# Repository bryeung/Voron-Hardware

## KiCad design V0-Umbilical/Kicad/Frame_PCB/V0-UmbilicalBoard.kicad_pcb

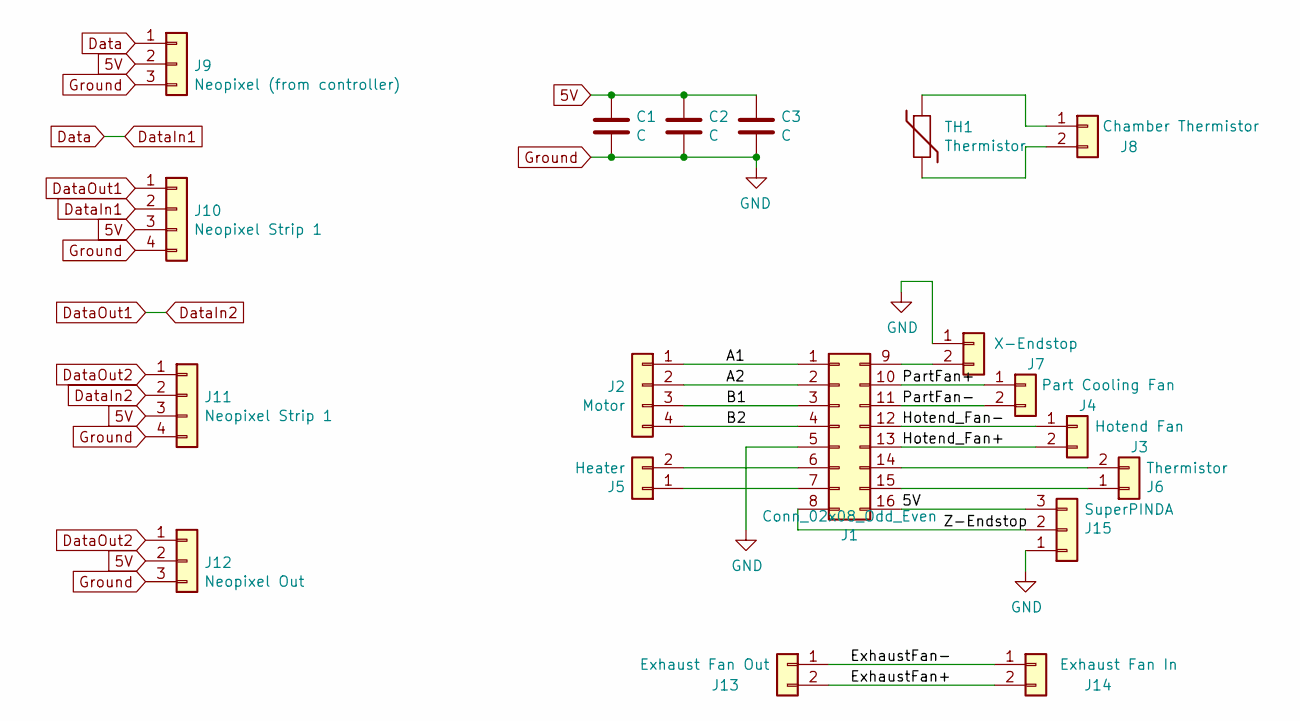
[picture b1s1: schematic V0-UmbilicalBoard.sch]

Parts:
C1, C2, C3: C; C_0805_2012Metric_Pad1.18x1.45mm_HandSolder
J1: Conn_02x08_Odd_Even; Molex_Micro-Fit_3.0_43045-1612_2x08_P3.00mm_Vertical
J2: Motor; JST_XH_B4B-XH-A_1x04_P2.50mm_Vertical
J3: Hotend Fan; JST_XH_B2B-XH-A_1x02_P2.50mm_Vertical
J4: Part Cooling Fan; JST_XH_B2B-XH-A_1x02_P2.50mm_Vertical
J5: Heater; TerminalBlock_Phoenix_MKDS-1,5-2-5.08_1x02_P5.08mm_Horizont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
J6: Thermistor; JST_XH_B2B-XH-A_1x02_P2.50mm_Vertical
J7: X-Endstop; JST_XH_B2B-XH-A_1x02_P2.50mm_Vertical
J8: Chamber Thermistor; JST_XH_B2B-XH-A_1x02_P2.50mm_Vertical
J9: Neopixel (from controller); JST_XH_B3B-XH-A_1x03_P2.50mm_Vertical
J10, J11: Neopixel Strip 1; JST_XH_B4B-XH-A_1x04_P2.50mm_Vertical
J12: Neopixel Out; JST_XH_B3B-XH-A_1x03_P2.50mm_Vertical
J13: Exhaust Fan Out; JST_XH_B2B-XH-A_1x02_P2.50mm_Vertical
J14: Exhaust Fan In; JST_XH_B2B-XH-A_1x02_P2.50mm_Vertical
J15: SuperPINDA; JST_XH_B3B-XH-A_1x03_P2.50mm_Vertical
TH1: Thermistor; R_0805_2012Metric_Pad1.20x1.40mm_HandSolder

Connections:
5V: C1.1, C2.1, C3.1, J1.16, J9.2, J10.3, J11.3, J12.2, J15.3
/A1: J1.1, J2.1
/A2: J1.2, J2.2
/B1: J1.3, J2.3
/B2: J1.4, J2.4
/ExhaustFan+: J13.2, J14.2
/ExhaustFan-: J13.1, J14.1
/Hotend_Fan+: J1.13, J3.2
/Hotend_Fan-: J1.12, J3.1
/PartFan+: J1.10, J4.1
/PartFan-: J1.11, J4.2
/Z-Endstop: J1.8, J15.2
Data: J9.1, J10.2
DataIn2: J10.1, J11.2
DataOut2: J11.1, J12.1
Ground: C1.2, C2.2, C3.2, J1.5, J7.1, J9.3, J10.4, J11.4, J12.3, J15.1
unnamed: J1.6, J5.2
unnamed: J1.7, J5.1
unnamed: J1.9, J7.2
unnamed: J1.14, J6.2
unnamed: J1.15, J6.1
unnamed: J8.1, TH1.1
unnamed: J8.2, TH1.2

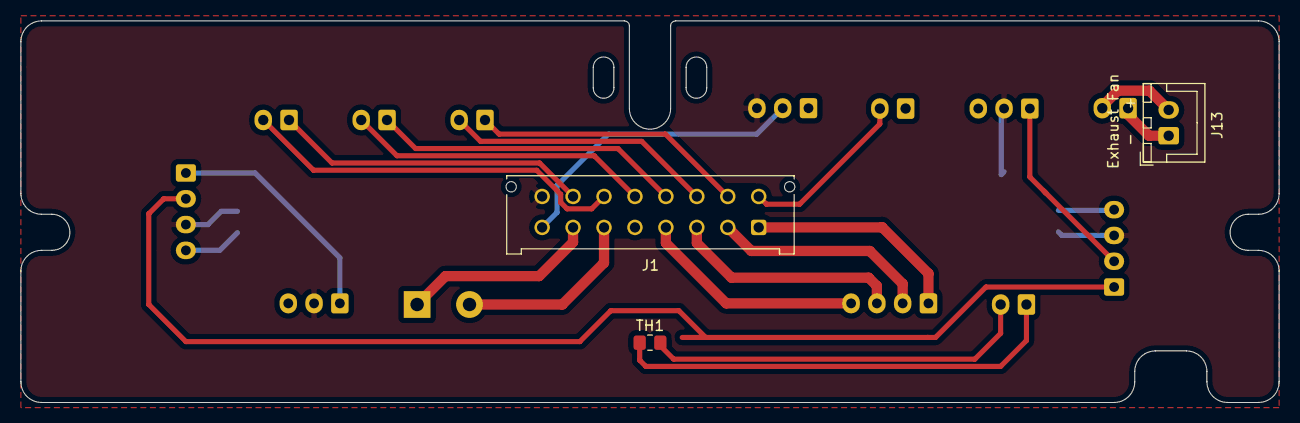
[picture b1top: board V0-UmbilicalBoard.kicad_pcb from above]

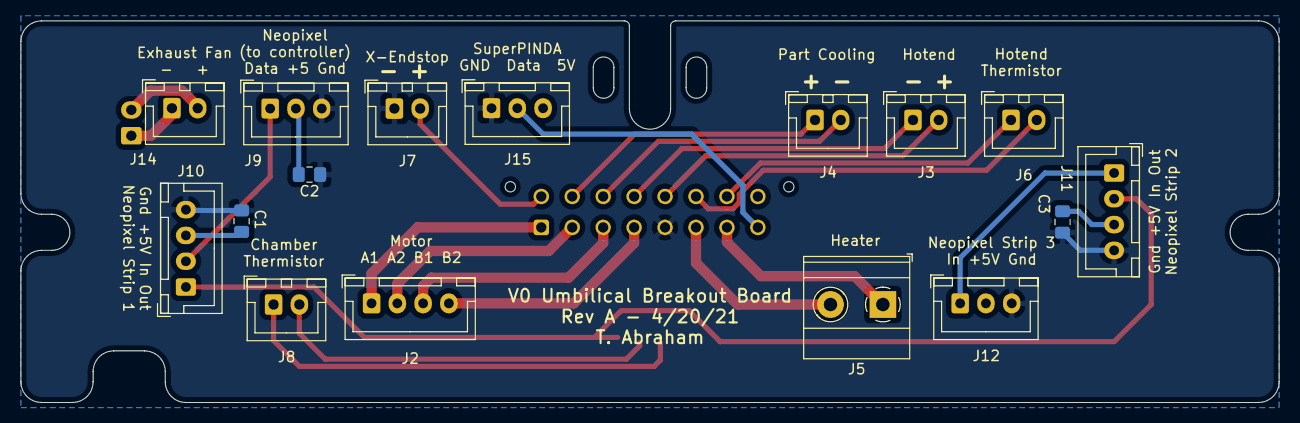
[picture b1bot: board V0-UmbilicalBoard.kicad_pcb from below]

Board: 2 copper layers, 122.0 x 37.0 mm, 19 parts (16 on the bottom side), 23 nets.

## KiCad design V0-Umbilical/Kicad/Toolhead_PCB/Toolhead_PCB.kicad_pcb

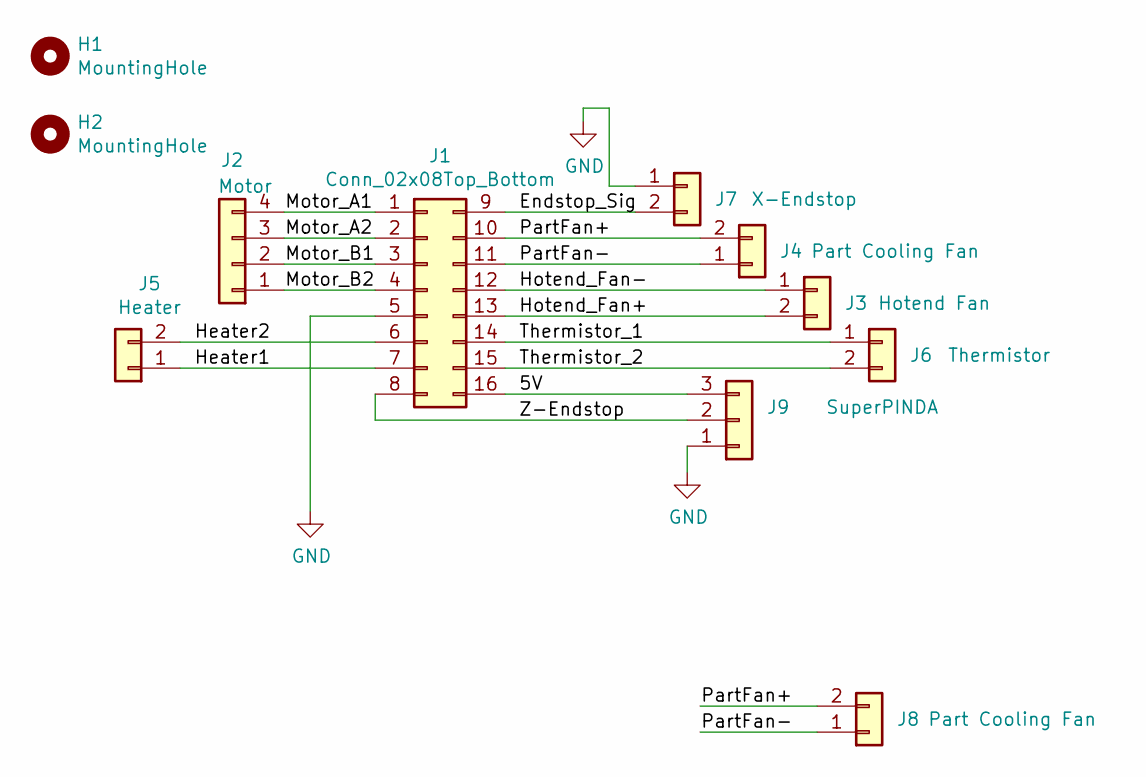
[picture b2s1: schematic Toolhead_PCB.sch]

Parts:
H1, H2: MountingHole; MountingHole_3.2mm_M3
J1: Conn_02x08Top_Bottom; Molex_Micro-Fit_3.0_43045-1600_2x08_P3.00mm_Horizontal
J2: Motor; JST_XH_B4B-XH-A_1x04_P2.50mm_Vertical
J3: Hotend Fan; JST_XH_B2B-XH-A_1x02_P2.50mm_Vertical
J4, J8: Part Cooling Fan; JST_XH_B2B-XH-A_1x02_P2.50mm_Vertical
J5: Heater; JST_XH_B2B-XH-A_1x02_P2.50mm_Vertical
J6: Thermistor; JST_XH_B2B-XH-A_1x02_P2.50mm_Vertical
J7: X-Endstop; JST_XH_B2B-XH-A_1x02_P2.50mm_Vertical
J9: SuperPINDA; JST_XH_B3B-XH-A_1x03_P2.50mm_Vertical

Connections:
/5V: J1.16, J9.3
/Endstop_Sig: J1.9, J7.2
/Heater1: J1.7, J5.1
/Heater2: J1.6, J5.2
/Hotend_Fan+: J1.13, J3.2
/Hotend_Fan-: J1.12, J3.1
/Motor_A1: J1.1, J2.4
/Motor_A2: J1.2, J2.3
/Motor_B1: J1.3, J2.2
/Motor_B2: J1.4, J2.1
/PartFan+: J1.10, J4.2, J8.2
/PartFan-: J1.11, J4.1, J8.1
/Thermistor_1: J1.14, J6.1
/Thermistor_2: J1.15, J6.2
/Z-Endstop: J1.8, J9.2
GND: J1.5, J7.1, J9.1

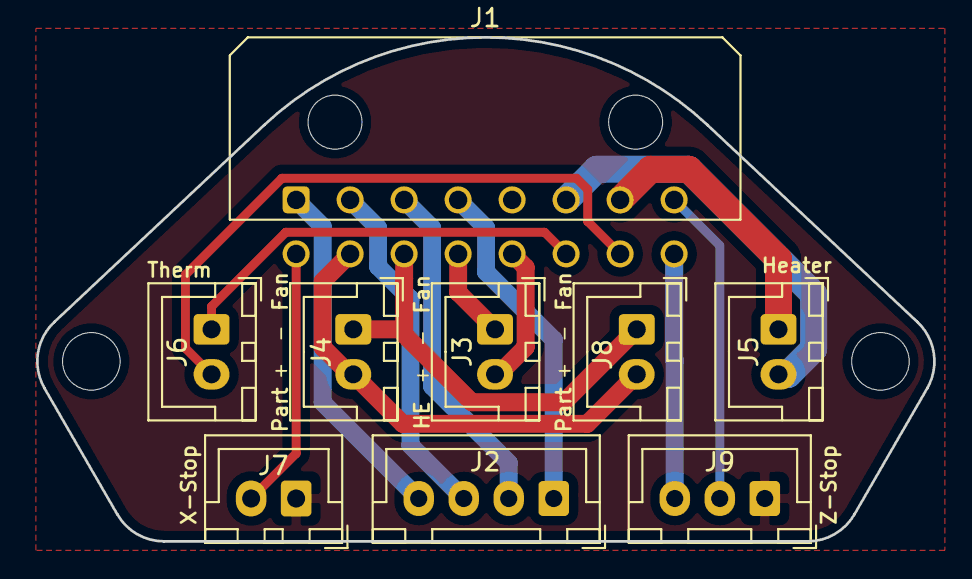
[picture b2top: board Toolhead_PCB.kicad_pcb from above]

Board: 2 copper layers, 49.8 x 28.0 mm, 11 parts (0 on the bottom side), 16 nets.

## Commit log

2021-06-24 First attempt at adding a SuperPINDA connector.
2021-06-25 Adding SuperPINDA and exhaust fan connectors.
2021-06-28 Clean up DRC errors.
2021-06-30 Fixed the exhaust fan headers colliding.
